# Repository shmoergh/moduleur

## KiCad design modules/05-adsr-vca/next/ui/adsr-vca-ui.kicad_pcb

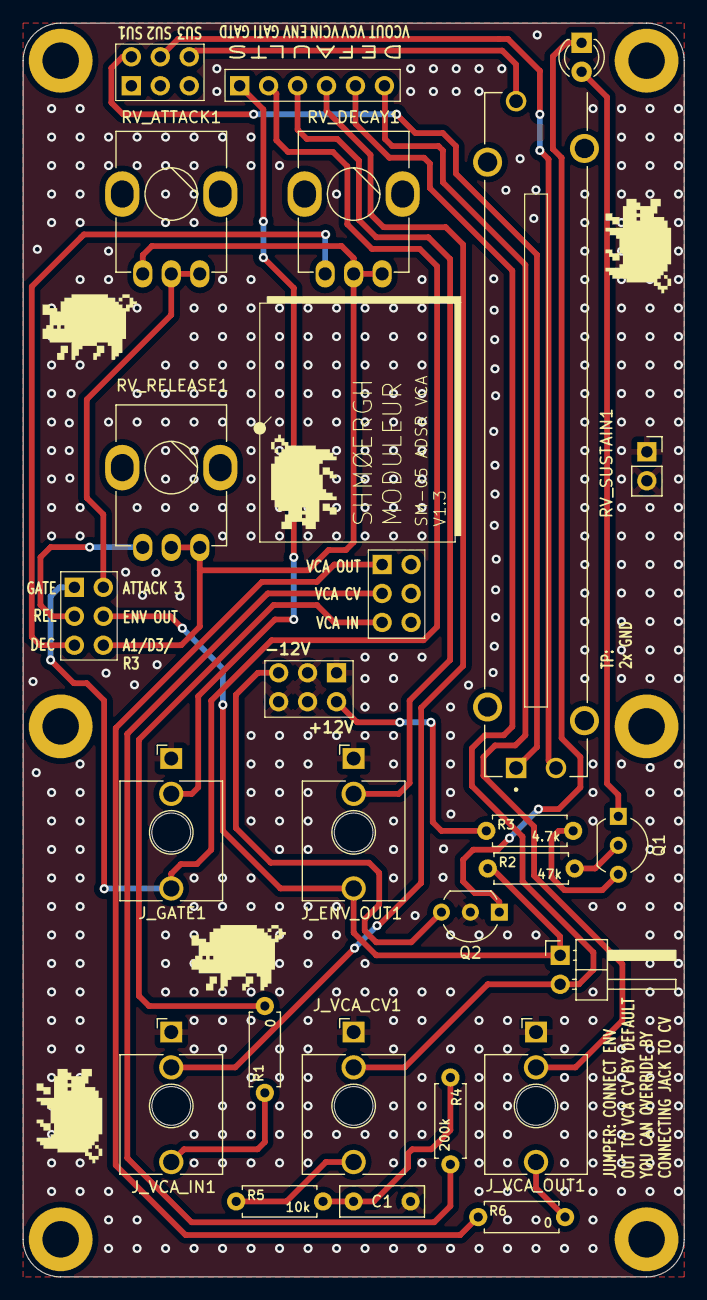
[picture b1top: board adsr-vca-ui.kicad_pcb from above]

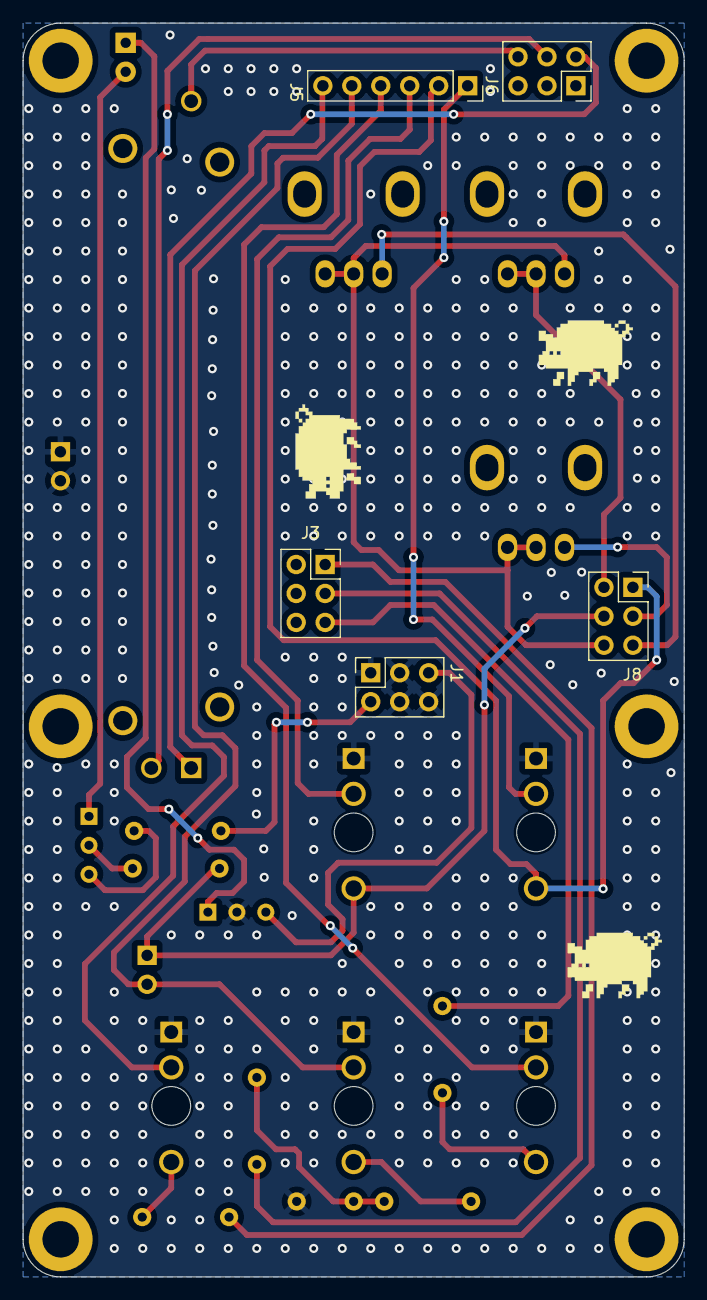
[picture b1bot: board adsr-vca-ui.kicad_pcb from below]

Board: 2 copper layers, 58.0 x 110.0 mm, 32 parts (5 on the bottom side), 28 nets.

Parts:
C1: 100nF; C_Rect_L7.2mm_W2.5mm_P5.00mm_FKS2_FKP2_MKS2_MKP2
D1: Red LED; LED_D3.0mm
H1, H2, H3, H4, H5, H6: MountingHole; MountingHole_3.2mm_M3_DIN965_Pad
J1, J3, J6, J8: Conn_02x03_Odd_Even; PinSocket_2x03_P2.54mm_Vertical
J4: Conn_01x02; PinSocket_1x02_P2.54mm_Vertical
J5: Conn_01x06; PinSocket_1x06_P2.54mm_Vertical
JP_DEFAULT_ENV_TO_VCA1: Jumper_2_Open; PinHeader_1x02_P2.54mm_Horizontal
J_ENV_OUT1: PJ398SM; Jack_3.5mm_QingPu_WQP-PJ398SM_Vertical_CircularHoles
J_GATE1: PJ398SM; Jack_3.5mm_QingPu_WQP-PJ398SM_Vertical_CircularHoles
J_VCA_CV1: PJ398SM; Jack_3.5mm_QingPu_WQP-PJ398SM_Vertical_CircularHoles
J_VCA_IN1: PJ398SM; Jack_3.5mm_QingPu_WQP-PJ398SM_Vertical_CircularHoles
J_VCA_OUT1: PJ398SM; Jack_3.5mm_QingPu_WQP-PJ398SM_Vertical_CircularHoles
Q1: 2N3904; TO-92_Inline_Wide
Q2: 2N3906; TO-92_Inline_Wide
R1, R6: 0; R_Axial_DIN0207_L6.3mm_D2.5mm_P7.62mm_Horizontal
R2: 47k; R_Axial_DIN0207_L6.3mm_D2.5mm_P7.62mm_Horizontal
R3: 4.7k; R_Axial_DIN0207_L6.3mm_D2.5mm_P7.62mm_Horizontal
R4: 200k; R_Axial_DIN0207_L6.3mm_D2.5mm_P7.62mm_Horizontal
R5: 10k; R_Axial_DIN0207_L6.3mm_D2.5mm_P7.62mm_Horizontal
RV_ATTACK1: A200k-1M; Potentiometer_Bourns_Single-PTV09A
RV_DECAY1: A200k-1M; Potentiometer_Bourns_Single-PTV09A
RV_RELEASE1: A200k-1M; Potentiometer_Bourns_Single-PTV09A
RV_SUSTAIN1: 10k; TRIM_PTA4543-2015DPB103

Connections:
+12V: J1.2, R3.1
-12V: J1.5, Q2.3 (C)
A1_D3_R3: J8.6, RV_ATTACK1.1, RV_DECAY1.2, RV_DECAY1.3, RV_RELEASE1.2, RV_RELEASE1.3
ATTACK_3: J8.2, RV_ATTACK1.2, RV_ATTACK1.3
DECAY_1: J8.5, RV_DECAY1.1
ENV_OUT: J8.4, JP_DEFAULT_ENV_TO_VCA1.1 (A), J_ENV_OUT1.T, R2.1
ENV_OUT_DEFAULT: J5.3, J_ENV_OUT1.TN
GATE: J5.2, J8.1, J_GATE1.T
GATE_DEFAULT: J5.1, J_GATE1.TN
GND: C1.2, J1.1, J1.3, J1.4, J1.6, J4.1, J4.2, J_ENV_OUT1.S, J_GATE1.S, J_VCA_CV1.S, J_VCA_IN1.S, J_VCA_OUT1.S, Q2.2 (B)
unnamed: C1.1, R4.1, R5.2
unnamed: D1.2 (A), Q1.1 (E)
unnamed: D1.1 (K), Q2.1 (E)
unnamed: J_VCA_CV1.T, R5.1
unnamed: J_VCA_IN1.T, R1.1
unnamed: J_VCA_OUT1.T, R6.2
unnamed: Q1.2 (B), R2.2
unnamed: Q1.3 (C), R3.2
RELEASE_1: J8.3, RV_RELEASE1.1
SUSTAIN_1: J6.2, RV_SUSTAIN1.1
SUSTAIN_2: J6.4, RV_SUSTAIN1.2
SUSTAIN_3: J6.6, RV_SUSTAIN1.3
VCA_CV: J3.3, R4.2
VCA_CV_DEFAULT: J5.5, JP_DEFAULT_ENV_TO_VCA1.2 (B), J_VCA_CV1.TN
VCA_IN: J3.5, R1.2
VCA_IN_DEFAULT: J5.4, J_VCA_IN1.TN
VCA_OUT: J3.1, R6.1
VCA_OUT_DEFAULT: J5.6, J_VCA_OUT1.TN

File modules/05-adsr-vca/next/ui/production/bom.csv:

Designator,Footprint,Quantity,Value,LCSC Part #
C1,C_Rect_L7.2mm_W2.5mm_P5.00mm_FKS2_FKP2_MKS2_MKP2,1,100nF,
D1,LED_D3.0mm,1,Red LED,
"J1, J3, J6, J8",PinSocket_2x03_P2.54mm_Vertical,4,Conn_02x03_Odd_Even,
J4,PinSocket_1x02_P2.54mm_Vertical,1,Conn_01x02,
J5,PinSocket_1x06_P2.54mm_Vertical,1,Conn_01x06,
JP_DEFAULT_ENV_TO_VCA1,PinHeader_1x02_P2.54mm_Horizontal,1,Jumper_2_Open,
"J_ENV_OUT1, J_GATE1, J_VCA_CV1, J_VCA_IN1, J_VCA_OUT1",Jack_3.5mm_QingPu_WQP-PJ398SM_Vertical_CircularHoles,5,PJ398SM,
Q1,TO-92_Inline_Wide,1,2N3904,
Q2,TO-92_Inline_Wide,1,2N3906,
"R1, R6",R_Axial_DIN0207_L6.3mm_D2.5mm_P7.62mm_Horizontal,2,0,
R2,R_Axial_DIN0207_L6.3mm_D2.5mm_P7.62mm_Horizontal,1,47k,
R3,R_Axial_DIN0207_L6.3mm_D2.5mm_P7.62mm_Horizontal,1,4.7k,
R4,R_Axial_DIN0207_L6.3mm_D2.5mm_P7.62mm_Horizontal,1,200k,
R5,R_Axial_DIN0207_L6.3mm_D2.5mm_P7.62mm_Horizontal,1,10k,
"RV_ATTACK1, RV_DECAY1, RV_RELEASE1",Potentiometer_Bourns_Single-PTV09A,3,A200k-1M,
RV_SUSTAIN1,TRIM_PTA4543-2015DPB103,1,10k,

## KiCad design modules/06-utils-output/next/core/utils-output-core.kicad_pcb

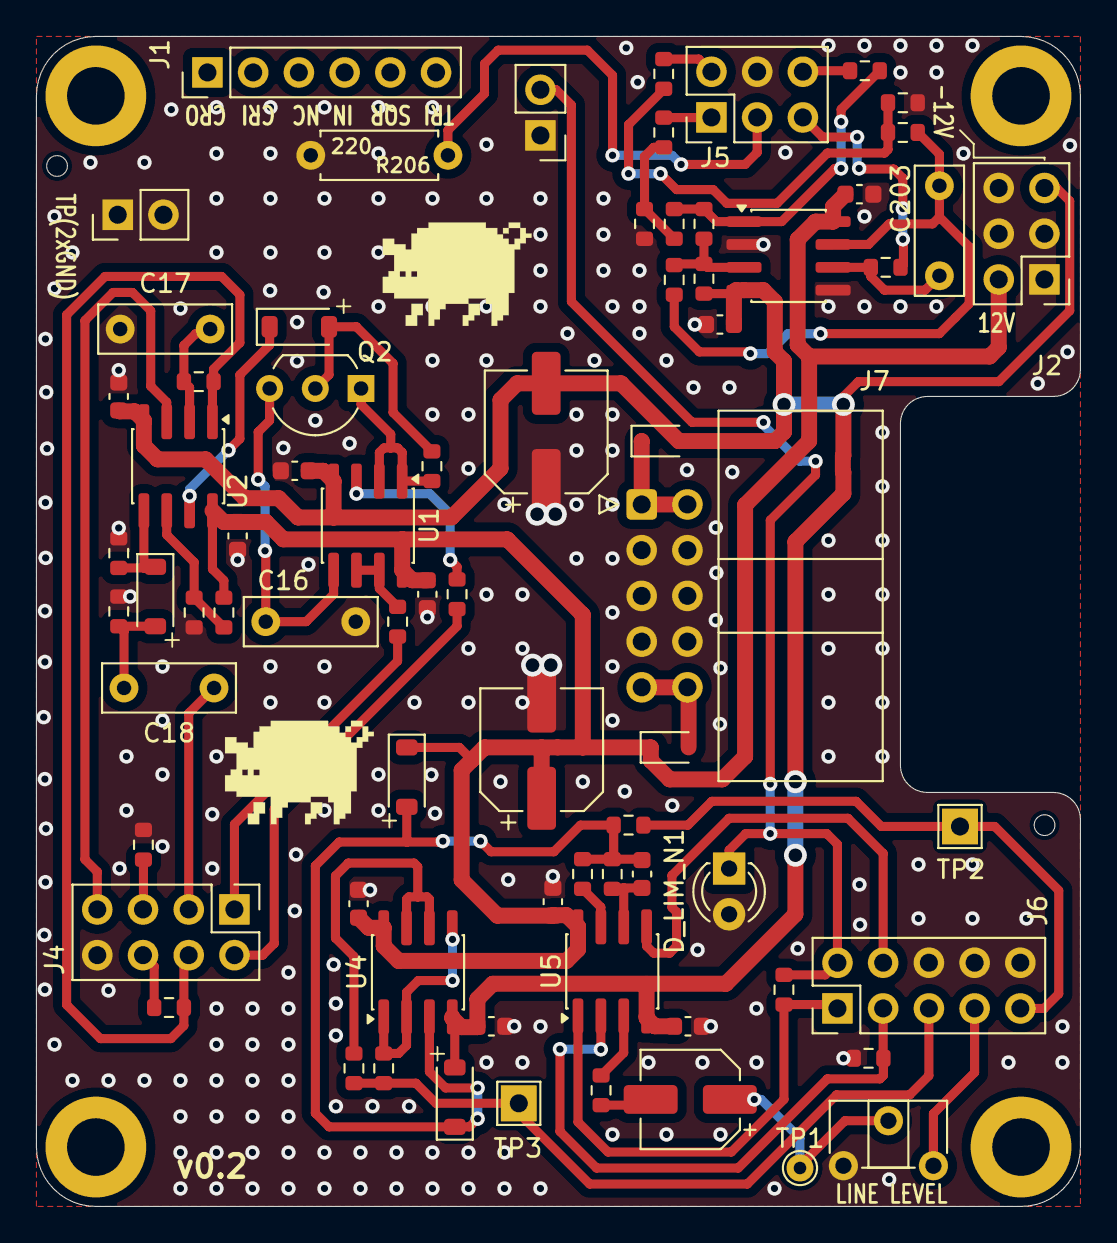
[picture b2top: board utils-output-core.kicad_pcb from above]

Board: 2 copper layers, 58.0 x 65.0 mm, 77 parts (0 on the bottom side), 48 nets.

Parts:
C1, C2, C3, C4, C10, C11, C12, C13, C201, C202: 100n; C_0603_1608Metric
C8, C9: 100u; CP_Elec_6.3x7.7
C14: 10u; CP_Elec_5x5.4
C15: 100p; C_0603_1608Metric
C16, C17: 100n (foil); C_Rect_L7.2mm_W2.5mm_P5.00mm_FKS2_FKP2_MKS2_MKP2
C18: 1n (foil); C_Rect_L7.2mm_W2.5mm_P5.00mm_FKS2_FKP2_MKS2_MKP2
C203: 3.3n (foil); C_Rect_L7.0mm_W2.5mm_P5.00mm
D1, D2: 1N5817; D_SOD-323
D3, D4, D15, D16: 1N4148; D_SOD-123
D_LIM_N1: Red LED; LED_D3.0mm
D_LIM_P1: Red LED; PinHeader_1x02_P2.54mm_Vertical
H1, H2, H3, H4: MountingHole; MountingHole_3.2mm_M3_DIN965_Pad
J1: Conn_01x06; PinHeader_1x06_P2.54mm_Vertical
J2, J5: Conn_02x03_Odd_Even; PinHeader_2x03_P2.54mm_Vertical
J3: Conn_01x02; PinHeader_1x02_P2.54mm_Vertical
J4: Conn_02x04_Odd_Even; PinHeader_2x04_P2.54mm_Vertical
J6: Conn_02x05_Odd_Even; PinHeader_2x05_P2.54mm_Vertical
J7: Conn_02x05_Odd_Even; IDC-Header_2x05_P2.54mm_Horizontal
Q2: 2N3819; TO-92_Inline_Wide
R1: 33k; R_0603_1608Metric
R10, R18, R29, R211: 10k; R_0603_1608Metric
R11, R20: 4.7k; R_0603_1608Metric
R12: 150; R_0603_1608Metric
R13, R17, R25, R208, R212: 1k; R_0603_1608Metric
R14, R15: 100; R_0603_1608Metric
R16, R209: 1M; R_0603_1608Metric
R19, R21, R22, R23, R205: 100k; R_0603_1608Metric
R24: 22k; R_0603_1608Metric
R201: 5.1M; R_0603_1608Metric
R202: 200k; R_0603_1608Metric
R203: 15k; R_0603_1608Metric
R204: 470k; R_0603_1608Metric
R206: 220; R_Axial_DIN0207_L6.3mm_D2.5mm_P7.62mm_Horizontal
R207: 12k; R_0603_1608Metric
R210: 2k; R_0603_1608Metric
RV_LINE_OUT_LVL1: 10k; Potentiometer_ACP_CA6-H2,5_Horizontal
TP1: MAX_LINEOUT; TestPoint_THTPad_D1.5mm_Drill0.7mm
TP2: MAINOUT; TestPoint_THTPad_2.0x2.0mm_Drill1.0mm
TP3: PHONES_OUT; TestPoint_THTPad_2.0x2.0mm_Drill1.0mm
U1, U2, U5, U201: TL072; SOIC-8_3.9x4.9mm_P1.27mm
U4: NE5532; SOIC-8_3.9x4.9mm_P1.27mm

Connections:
+12V: C1.1, C3.1, C8.1, C10.1, C12.1, C201.1, D1.1 (K), D15.1 (K), J2.2, R22.2, U1.8 (V+), U2.8 (V+), U4.8 (V+), U5.8 (V+), U201.8 (V+)
-12V: C2.2, C4.2, C9.2, C11.2, C13.2, C202.2, D2.2 (A), D16.2 (A), J2.5, R201.1, U1.4 (V-), U2.4 (V-), U4.4 (V-), U5.4 (V-), U201.4 (V-)
CRUSH_IN: J4.2, R10.1
CRUSH_OUT: J4.1, R17.2
CRUSH_TRIG: C18.1, J4.3
CRUSH_TRIG_DEFAULT: J4.4, R18.2, R19.2, U2.1
GND: C1.2, C2.1, C3.2, C4.1, C8.2, C9.1, C10.2, C11.1, C12.2, C13.1, C16.2, C17.2, C201.2, C202.1, D_LIM_N1.2 (A), D_LIM_P1.1 (K), J2.1, J2.3, J2.4, J2.6, J3.1, J3.2, J4.8, J5.4, J6.6, J6.8, J6.10, J7.3, J7.4, J7.5, J7.6, J7.7, J7.8, R1.1, R20.1, R21.1, R23.1, R24.1, R206.2, R207.2, R211.2, RV_LINE_OUT_LVL1.1, U201.2 (-), U201.5 (+)
LFO_POT_1: J5.3, R206.1
LFO_POT_2: J5.5, R209.2
LFO_POT_3: J5.6, R204.1
LFO_SQR: J5.1, R208.2
LFO_TRI: J5.2, R212.2
unnamed: R17.1, U1.6 (-), U1.7
unnamed: R10.2, U1.3 (+)
unnamed: R29.1, U5.3 (+)
unnamed: C14.1, RV_LINE_OUT_LVL1.2, TP1.1
unnamed: C14.2, R29.2
unnamed: C203.1, R205.2, R210.1, U201.7
unnamed: D1.2 (A), J7.9, J7.10
unnamed: D2.1 (K), J7.1, J7.2
unnamed: C18.2, D3.2 (A), R21.2
unnamed: D3.1 (K), R23.2, U2.5 (+)
unnamed: D4.2 (A), Q2.2 (G), R16.1
unnamed: D4.1 (K), U2.7
unnamed: C15.2, D15.2 (A), D16.1 (K), R11.1, R12.1, R13.1, U4.3 (+)
unnamed: Q2.1 (D), R16.2, U1.1, U1.2 (-)
unnamed: C16.1, Q2.3 (S), U1.5 (+)
unnamed: R12.2, U5.7
unnamed: R202.2, R203.1, R204.2, U201.1
unnamed: R203.2, R207.1, R208.1
unnamed: R210.2, R211.1, R212.1
unnamed: C17.1, R18.1, U2.2 (-)
unnamed: R1.2, R22.1, U2.6 (-)
unnamed: R15.2, U4.1, U4.2 (-), U4.5 (+)
unnamed: R14.2, U4.6 (-), U4.7
unnamed: C15.1, R11.2, U5.6 (-)
unnamed: R201.2, R202.1, R205.1, U201.3 (+)
unnamed: C203.2, R209.1, U201.6 (-)
OUTPUT_DRIVE_1: J6.3, R24.2, U5.2 (-)
OUTPUT_DRIVE_3: J6.1, R25.2, U5.1
OUTPUT_IN: J6.7, RV_LINE_OUT_LVL1.3
OUTPUT_LINE_OUT: J6.9, R13.2, TP2.1
OUTPUT_PHONES_OUT: J6.5, R14.1, R15.1, TP3.1
OUTPUT_VOL_2: J6.4, U5.5 (+)
OUTPUT_VOL_3: D_LIM_N1.1 (K), D_LIM_P1.2 (A), J6.2, R25.1
RV_CRUSH_1: J4.5, R20.2
RV_CRUSH_2: J4.7, U2.3 (+)
RV_CRUSH_3: J4.6, R19.1

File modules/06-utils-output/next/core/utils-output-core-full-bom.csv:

"Reference","Qty","Value","Exclude from BOM","Footprint","LCSC","Mouser Part no.","Part URL","Vendor","CHECKED"
"C1,C2,C3,C4,C10,C11,C12,C13,C201,C202","10","100n","","Capacitor_SMD:C_0603_1608Metric","C14663","","","JLCPCB","YES"
"C8,C9","2","100u","","Capacitor_SMD:CP_Elec_6.3x7.7","C2836442","","","JLCPCB","YES"
"C14","1","10u","","Capacitor_SMD:CP_Elec_5x5.4","C4747971","","","JLCPCB","YES"
"C15","1","100p","","Capacitor_SMD:C_0603_1608Metric","C14858","","","JLCPCB","YES"
"C16,C17","2","100n (foil)","","Capacitor_THT:C_Rect_L7.2mm_W2.5mm_P5.00mm_FKS2_FKP2_MKS2_MKP2","","80-MMK5104J50J01L16 ","https://mou.sr/4iTinUl","Mouser","YES"
"C18","1","1n (foil)","","Capacitor_THT:C_Rect_L7.2mm_W2.5mm_P5.00mm_FKS2_FKP2_MKS2_MKP2","","80-MMK5102M50J01L4 ","https://mou.sr/4rSWoRD","Mouser","YES"
"C203","1","3.3n (foil)","","Capacitor_THT:C_Rect_L7.0mm_W2.5mm_P5.00mm","","80-R82EC1330AA50K ","https://mou.sr/3BhmOHr","Mouser","YES]"
"D1,D2","2","1N5817","","Diode_SMD:D_SOD-323","C5190152","","","JLCPCB","YES"
"D3,D4,D15,D16","4","1N4148","","Diode_SMD:D_SOD-123","C81598","","","JLCPCB","YES"
"D_LIM_N1","1","Red LED","","LED_THT:LED_D3.0mm","","","","Mouser",""
"D_LIM_P1","1","Red LED","","LED_THT:LED_D5.0mm","","","","Mouser",""
"H1,H2,H3,H4","4","MountingHole","Excluded from BOM","MountingHole:MountingHole_3.2mm_M3_DIN965_Pad","","","","-",""
"J1","1","Conn_01x06","","Connector_PinHeader_2.54mm:PinHeader_1x06_P2.54mm_Vertical","","200-SSW10601TMS","https://mou.sr/4puxA0F","Mouser",""
"J2,J5","2","Conn_02x03_Odd_Even","","Connector_PinHeader_2.54mm:PinHeader_2x03_P2.54mm_Vertical","","200-TSW10307TD","https://mou.sr/4liCQlU","Mouser",""
"J3","1","Conn_01x02","","Connector_PinHeader_2.54mm:PinHeader_1x02_P2.54mm_Vertical","","200-HTSW10207TS","https://mou.sr/3IruU3e","Mouser",""
"J4","1","Conn_02x04_Odd_Even","","Connector_PinHeader_2.54mm:PinHeader_2x04_P2.54mm_Vertical","","200-HTSW10407TD","https://mou.sr/4nYsZDt","Mouser",""
"J6","1","Conn_02x05_Odd_Even","","Connector_PinHeader_2.54mm:PinHeader_2x05_P2.54mm_Vertical","","200-TSW10507TD","https://mou.sr/40QhDaC","Mouser",""
"J7","1","Conn_02x05_Odd_Even","","Connector_IDC:IDC-Header_2x05_P2.54mm_Horizontal","","571-5103310-1","https://mou.sr/3GwYxj9","Mouser",""
"Q2","1","2N3819","","Package_TO_SOT_THT:TO-92_Inline_Wide","","610-2N3819","https://mou.sr/4rVtQ9Z","Mouser",""
"R1","1","33k","","Resistor_SMD:R_0603_1608Metric","C4216","","","JLCPCB","YES"
"R10,R18,R29,R211","4","10k","","Resistor_SMD:R_0603_1608Metric","C25804","","","JLCPCB","YES"
"R11,R20","2","4.7k","","Resistor_SMD:R_0603_1608Metric","C23162","","","JLCPCB","YES"
"R12","1","150","","Resistor_SMD:R_0603_1608Metric","C22808","","","JLCPCB","YES"
"R13,R17,R25,R208,R212","5","1k","","Resistor_SMD:R_0603_1608Metric","C21190","","","JLCPCB","YES"
"R14,R15","2","100","","Resistor_SMD:R_0603_1608Metric","C22775","","","JLCPCB","YES"
"R16,R209","2","1M","","Resistor_SMD:R_0603_1608Metric","C22935","","","JLCPCB","YES"
"R19,R21,R22,R23,R205","5","100k","","Resistor_SMD:R_0603_1608Metric","C25803","","","JLCPCB","YES"
"R24","1","22k","","Resistor_SMD:R_0603_1608Metric","C31850","","","JLCPCB","YES"
"R201","1","5.1M","","Resistor_SMD:R_0603_1608Metric","C13320","","","JLCPCB","YES"
"R202","1","200k","","Resistor_SMD:R_0603_1608Metric","C25811","","","JLCPCB","YES"
"R203","1","15k","","Resistor_SMD:R_0603_1608Metric","C22809","","","JLCPCB","YES"
"R204","1","470k","","Resistor_SMD:R_0603_1608Metric","C23178","","","JLCPCB","YES"
"R206","1","220","","Shmoergh_Custom_Footprints:R_Axial_DIN0207_L6.3mm_D2.5mm_P7.62mm_Horizontal","","603-MFR-25FTF52-220R ","https://mou.sr/3XROtWU","Mouser",""
"R207","1","12k","","Resistor_SMD:R_0603_1608Metric","C22790","","","JLCPCB","YES"
"R210","1","2k","","Resistor_SMD:R_0603_1608Metric","C22975","","","JLCPCB","YES"
"RV_LINE_OUT_LVL1","1","10k","","Potentiometer_THT:Potentiometer_ACP_CA6-H2,5_Horizontal","","774-06TR4AA103CP","https://mou.sr/44pTlq5","Mouser",""
"TP1","1","MAX_LINEOUT","Excluded from BOM","TestPoint:TestPoint_THTPad_D1.5mm_Drill0.7mm","","","","-",""
"TP2","1","MAINOUT","Excluded from BOM","TestPoint:TestPoint_THTPad_2.0x2.0mm_Drill1.0mm","","","","-",""
"TP3","1","PHONES_OUT","Excluded from BOM","TestPoint:TestPoint_THTPad_2.0x2.0mm_Drill1.0mm","","","","-",""
"U1,U2,U5,U201","4","TL072","","Package_SO:SOIC-8_3.9x4.9mm_P1.27mm","C6961","","","JLCPCB","YES"
"U4","1","NE5532","","Package_SO:SOIC-8_3.9x4.9mm_P1.27mm","C7426","","","JLCPCB","YES"

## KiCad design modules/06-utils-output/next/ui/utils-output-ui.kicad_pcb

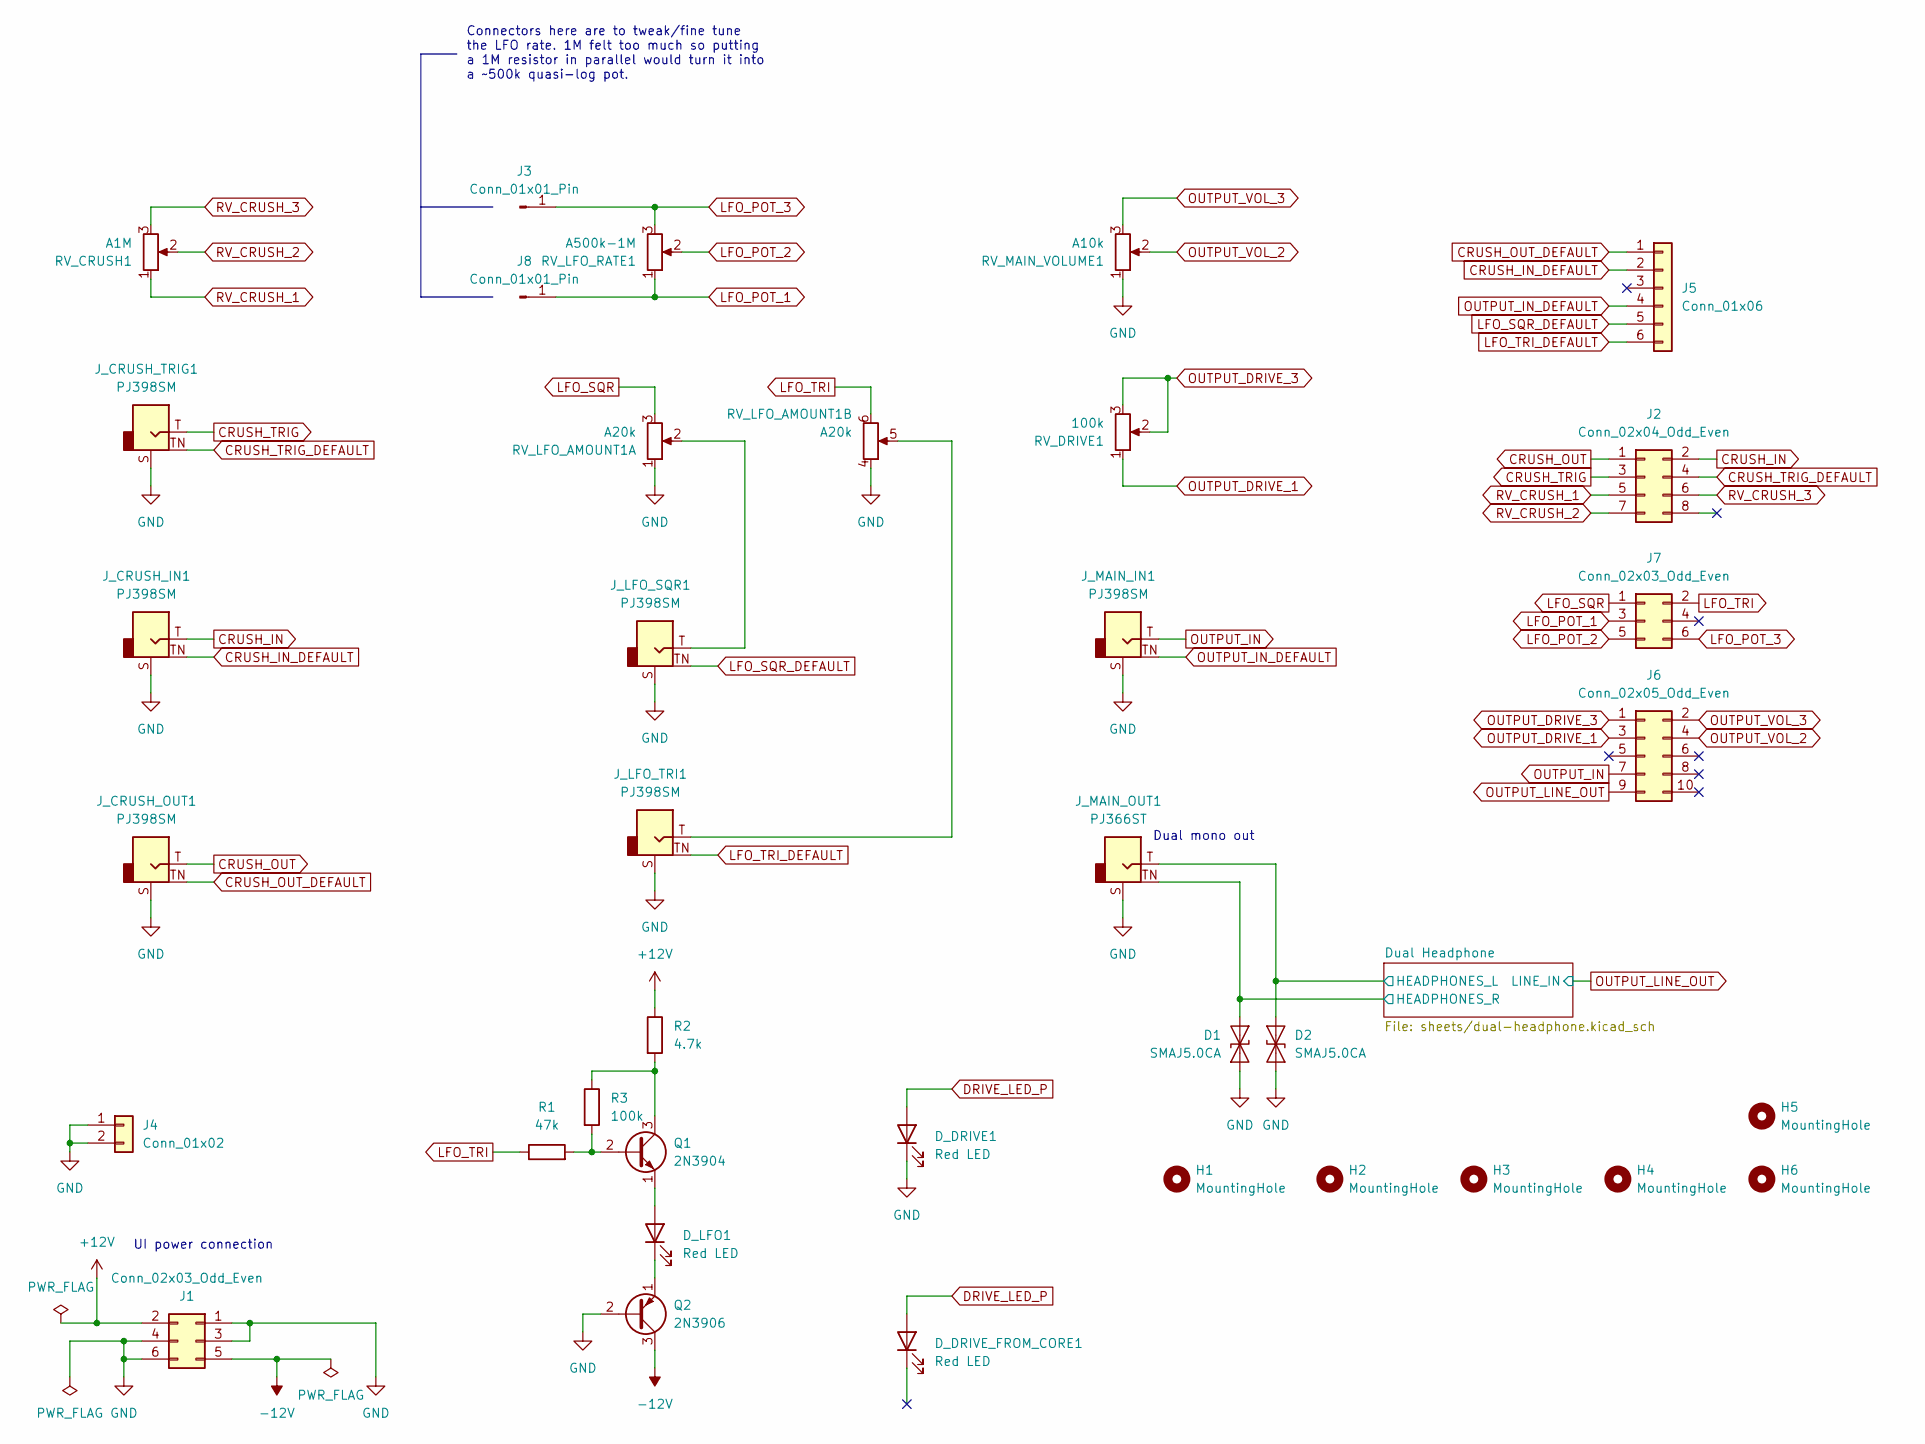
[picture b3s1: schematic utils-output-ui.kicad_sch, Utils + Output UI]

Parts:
D1, D2: SMAJ5.0CA; D_SMA
D_DRIVE1: Red LED; LED_D3.0mm
D_DRIVE_FROM_CORE1: Red LED; PinSocket_1x02_P2.54mm_Vertical
D_LFO1: Red LED; LED_D3.0mm
H1, H2, H3, H4, H5, H6: MountingHole; MountingHole_3.2mm_M3_DIN965_Pad
J1, J7: Conn_02x03_Odd_Even; PinSocket_2x03_P2.54mm_Vertical; Part no. 200-SSW10301TD
J2: Conn_02x04_Odd_Even; PinSocket_2x04_P2.54mm_Vertical; Part no. 200-SSW10401TD
J3, J8: Conn_01x01_Pin; TestPoint_THTPad_D2.0mm_Drill1.0mm
J4: Conn_01x02; PinSocket_1x02_P2.54mm_Vertical; Part no. 200-SSW10201TS
J5: Conn_01x06; PinSocket_1x06_P2.54mm_Vertical; Part no. 200-SSW10601TS
J6: Conn_02x05_Odd_Even; PinSocket_2x05_P2.54mm_Vertical; Part no. 200-SSW10501TD
J_CRUSH_IN1: PJ398SM; Jack_3.5mm_QingPu_WQP-PJ398SM_Vertical_CircularHoles; Part no. PJ398SM
J_CRUSH_OUT1: PJ398SM; Jack_3.5mm_QingPu_WQP-PJ398SM_Vertical_CircularHoles; Part no. PJ398SM
J_CRUSH_TRIG1: PJ398SM; Jack_3.5mm_QingPu_WQP-PJ398SM_Vertical_CircularHoles; Part no. PJ398SM
J_LFO_SQR1: PJ398SM; Jack_3.5mm_QingPu_WQP-PJ398SM_Vertical_CircularHoles; Part no. PJ398SM
J_LFO_TRI1: PJ398SM; Jack_3.5mm_QingPu_WQP-PJ398SM_Vertical_CircularHoles; Part no. PJ398SM
J_MAIN_IN1: PJ398SM; Jack_3.5mm_QingPu_WQP-PJ398SM_Vertical_CircularHoles; Part no. PJ398SM
J_MAIN_OUT1: PJ366ST; Jack_3.5mm_QingPu_WQP-PJ398SM_Vertical_CircularHoles; Part no. PJ366ST
Q1: 2N3904; TO-92_Inline_Wide; Part no. 637-2N3904
Q2: 2N3906; TO-92_Inline_Wide; Part no. 637-2N3906
R1: 47k; R_Axial_DIN0207_L6.3mm_D2.5mm_P7.62mm_Horizontal; Part no. 603-MFR-25FRF52-47K
R2: 4.7k; R_Axial_DIN0207_L6.3mm_D2.5mm_P7.62mm_Horizontal; Part no. 603-MFR25SFTF52-4K7
R3: 100k; R_Axial_DIN0207_L6.3mm_D2.5mm_P7.62mm_Horizontal; Part no. 603-MFR25SFTF52-4K7
RV_CRUSH1: A1M; Potentiometer_Bourns_Single-PTV09A; Part no. 652-PTV09A4025FA105
RV_DRIVE1: 100k; Potentiometer_Bourns_Single-PTV09A; Part no. 652-PTV09A4025UB104
RV_LFO_AMOUNT1: A20k; Potentiometer_Bourns_Dual-PTV112-4; Part No. 652-PTV1124425AA203
RV_LFO_RATE1: A500k-1M; Potentiometer_Bourns_Single-PTV09A; Part no. 652-PTV09A4025FA105
RV_MAIN_VOLUME1: A10k; Potentiometer_Bourns_Single-PTV09A; Part no. 652-PTV09A4025FA103

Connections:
+12V: J1.2, R2.1; also elsewhere on the board
-12V: J1.5, Q2.3 (C); also elsewhere on the board
/Dual Headphone/HEADPHONES_L: D2.2 (A2), J_MAIN_OUT1.T; also elsewhere on the board
/Dual Headphone/HEADPHONES_R: D1.2 (A2), J_MAIN_OUT1.TN; also elsewhere on the board
CRUSH_IN: J2.2, J_CRUSH_IN1.T
CRUSH_IN_DEFAULT: J5.2, J_CRUSH_IN1.TN
CRUSH_OUT: J2.1, J_CRUSH_OUT1.T
CRUSH_OUT_DEFAULT: J5.1, J_CRUSH_OUT1.TN
CRUSH_TRIG: J2.3, J_CRUSH_TRIG1.T
CRUSH_TRIG_DEFAULT: J2.4, J_CRUSH_TRIG1.TN
DRIVE_LED_P: D_DRIVE1.2 (A), D_DRIVE_FROM_CORE1.2 (A)
GND: D1.1 (A1), D2.1 (A1), D_DRIVE1.1 (K), J1.1, J1.3, J1.4, J1.6, J4.1, J4.2, J_CRUSH_IN1.S, J_CRUSH_OUT1.S, J_CRUSH_TRIG1.S, J_LFO_SQR1.S, J_LFO_TRI1.S, J_MAIN_IN1.S, J_MAIN_OUT1.S, Q2.2 (B), RV_LFO_AMOUNT1.1, RV_LFO_AMOUNT1.4, RV_MAIN_VOLUME1.1; also elsewhere on the board
LFO_POT_1: J7.3, J8.1, RV_LFO_RATE1.1
LFO_POT_2: J7.5, RV_LFO_RATE1.2
LFO_POT_3: J3.1, J7.6, RV_LFO_RATE1.3
LFO_SQR: J7.1, RV_LFO_AMOUNT1.3
LFO_SQR_DEFAULT: J5.5, J_LFO_SQR1.TN
LFO_TRI: J7.2, R1.1, RV_LFO_AMOUNT1.6
LFO_TRI_DEFAULT: J5.6, J_LFO_TRI1.TN
unnamed: D_LFO1.2 (A), Q1.1 (E)
unnamed: D_LFO1.1 (K), Q2.1 (E)
unnamed: J_LFO_SQR1.T, RV_LFO_AMOUNT1.2
unnamed: J_LFO_TRI1.T, RV_LFO_AMOUNT1.5
unnamed: Q1.2 (B), R1.2, R3.2
unnamed: Q1.3 (C), R2.2, R3.1
OUTPUT_DRIVE_1: J6.3, RV_DRIVE1.1
OUTPUT_DRIVE_3: J6.1, RV_DRIVE1.2, RV_DRIVE1.3
OUTPUT_IN: J6.7, J_MAIN_IN1.T
OUTPUT_IN_DEFAULT: J5.4, J_MAIN_IN1.TN
OUTPUT_LINE_OUT: J6.9; also elsewhere on the board
OUTPUT_VOL_2: J6.4, RV_MAIN_VOLUME1.2
OUTPUT_VOL_3: J6.2, RV_MAIN_VOLUME1.3
RV_CRUSH_1: J2.5, RV_CRUSH1.1
RV_CRUSH_2: J2.7, RV_CRUSH1.2
RV_CRUSH_3: J2.6, RV_CRUSH1.3

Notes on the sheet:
Dual mono out
Connectors here are to tweak/fine tune the LFO rate. 1M felt too much so putting a 1M resistor in parallel would turn it into a ~500k quasi-log pot.
UI power connection

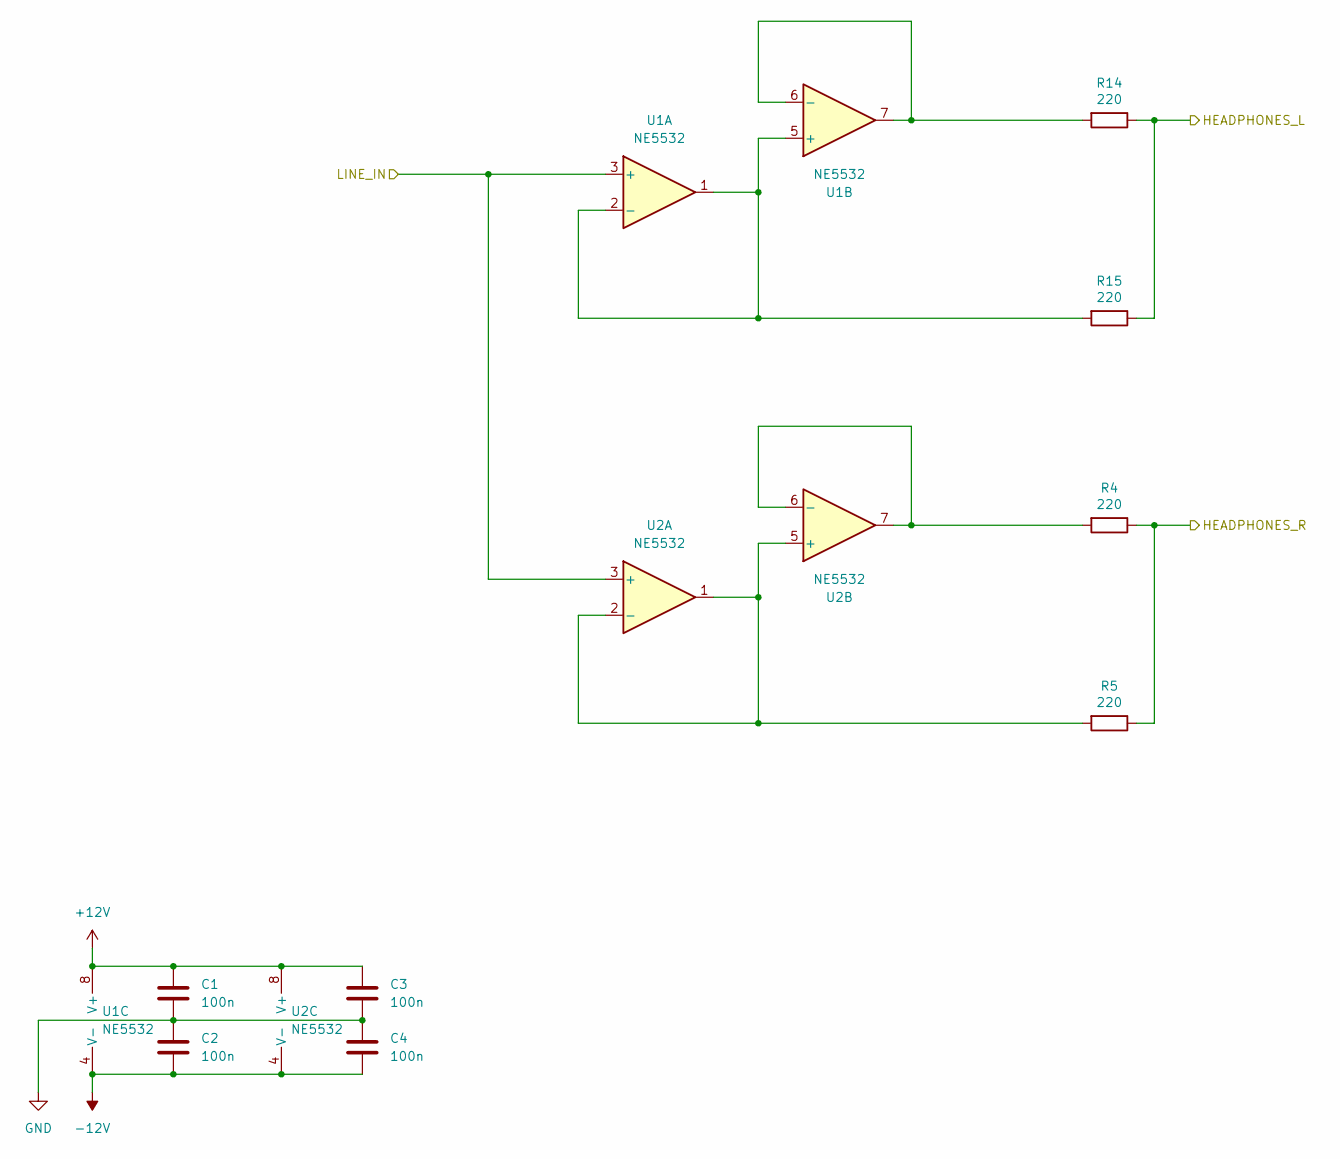
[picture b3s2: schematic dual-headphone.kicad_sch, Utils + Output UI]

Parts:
C1, C2, C3, C4: 100n; C_1206_3216Metric_Pad1.33x1.80mm_HandSolder; Part No. 80-C1206C104J5RAC
R4, R5, R14, R15: 220; R_1206_3216Metric_Pad1.30x1.75mm_HandSolder; Part No. 652-CR1206JW-221ELF
U1, U2: NE5532; SOIC-8_3.9x4.9mm_P1.27mm; Part No. 595-NE5532DR

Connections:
+12V: C1.1, C3.1, U1.8 (V+), U2.8 (V+); also elsewhere on the board
-12V: C2.2, C4.2, U1.4 (V-), U2.4 (V-); also elsewhere on the board
/Dual Headphone/HEADPHONES_L: R14.1, R15.1; also elsewhere on the board
/Dual Headphone/HEADPHONES_R: R4.1, R5.1; also elsewhere on the board
GND: C1.2, C2.1, C3.2, C4.1; also elsewhere on the board
unnamed: R15.2, U1.1, U1.2 (-), U1.5 (+)
unnamed: R14.2, U1.6 (-), U1.7
unnamed: R5.2, U2.1, U2.2 (-), U2.5 (+)
unnamed: R4.2, U2.6 (-), U2.7
OUTPUT_LINE_OUT: U1.3 (+), U2.3 (+); also elsewhere on the board

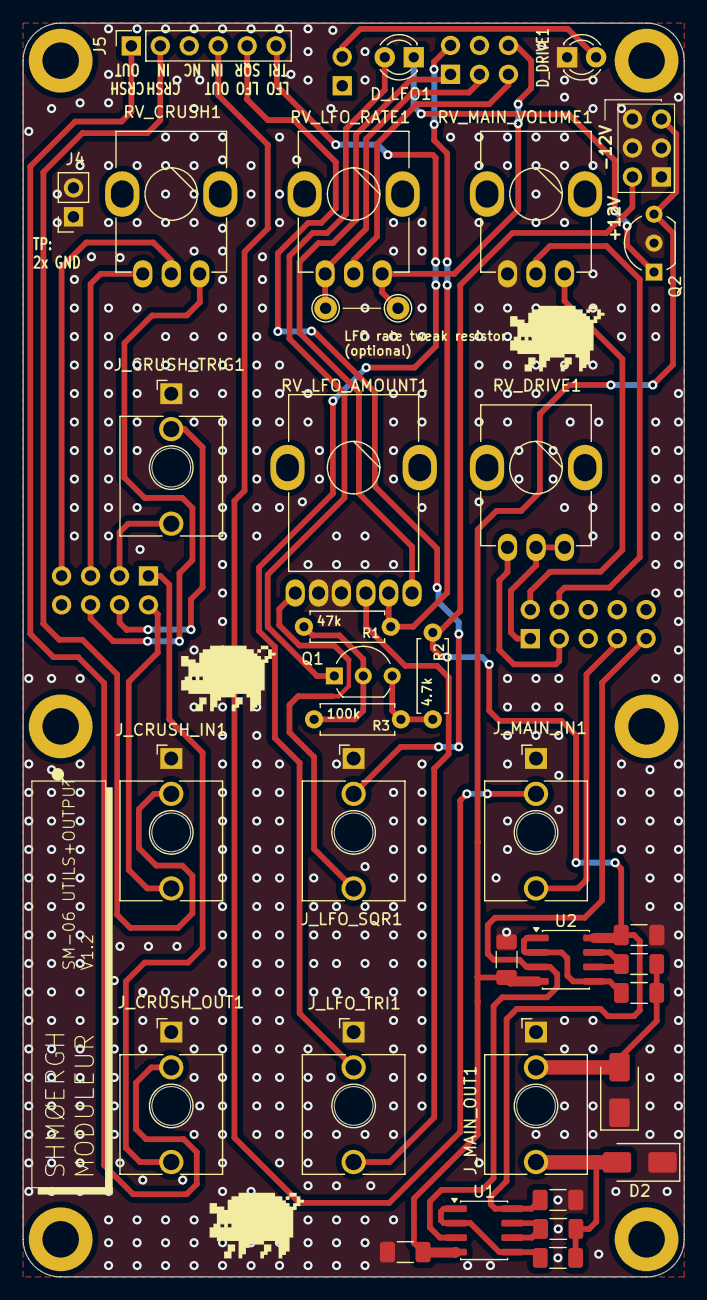
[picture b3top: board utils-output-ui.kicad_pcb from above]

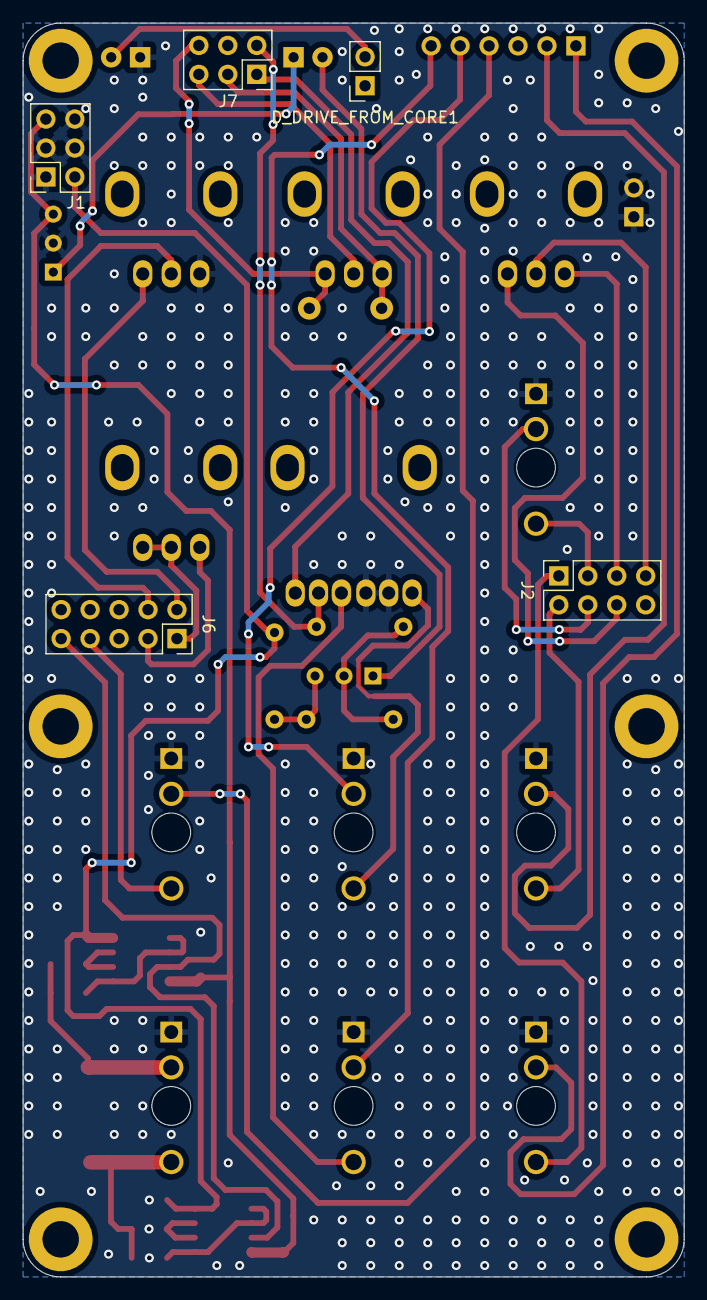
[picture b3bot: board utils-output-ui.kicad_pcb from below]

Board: 2 copper layers, 58.0 x 110.0 mm, 46 parts (5 on the bottom side), 39 nets.

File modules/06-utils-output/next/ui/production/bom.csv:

Designator,Footprint,Quantity,Value,LCSC Part #
"C1, C2, C3, C4",1206,4,100n,
"D1, D2",D_SMA,2,SMAJ5.0CA,
"D_DRIVE1, D_LFO1",LED_D3.0mm,2,Red LED,
D_DRIVE_FROM_CORE1,PinSocket_1x02_P2.54mm_Vertical,1,Red LED,
"J1, J7",PinSocket_2x03_P2.54mm_Vertical,2,Conn_02x03_Odd_Even,
J2,PinSocket_2x04_P2.54mm_Vertical,1,Conn_02x04_Odd_Even,
"J3, J8",TestPoint_THTPad_D2.0mm_Drill1.0mm,2,Conn_01x01_Pin,
J4,PinSocket_1x02_P2.54mm_Vertical,1,Conn_01x02,
J5,PinSocket_1x06_P2.54mm_Vertical,1,Conn_01x06,
J6,PinSocket_2x05_P2.54mm_Vertical,1,Conn_02x05_Odd_Even,
"J_CRUSH_IN1, J_CRUSH_OUT1, J_CRUSH_TRIG1, J_LFO_SQR1, J_LFO_TRI1, J_MAIN_IN1",Jack_3.5mm_QingPu_WQP-PJ398SM_Vertical_CircularHoles,6,PJ398SM,
J_MAIN_OUT1,Jack_3.5mm_QingPu_WQP-PJ398SM_Vertical_CircularHoles,1,PJ366ST,
Q1,TO-92_Inline_Wide,1,2N3904,
Q2,TO-92_Inline_Wide,1,2N3906,
R1,R_Axial_DIN0207_L6.3mm_D2.5mm_P7.62mm_Horizontal,1,47k,
"R14, R15, R4, R5",1206,4,220,
R2,R_Axial_DIN0207_L6.3mm_D2.5mm_P7.62mm_Horizontal,1,4.7k,
R3,R_Axial_DIN0207_L6.3mm_D2.5mm_P7.62mm_Horizontal,1,100k,
RV_CRUSH1,Potentiometer_Bourns_Single-PTV09A,1,A1M,
RV_DRIVE1,Potentiometer_Bourns_Single-PTV09A,1,100k,
RV_LFO_AMOUNT1,Potentiometer_Bourns_Dual-PTV112-4,1,A20k,
RV_LFO_RATE1,Potentiometer_Bourns_Single-PTV09A,1,A500k-1M,
RV_MAIN_VOLUME1,Potentiometer_Bourns_Single-PTV09A,1,A10k,
"U1, U2",SOIC-8_3.9x4.9mm_P1.27mm,2,NE5532,
